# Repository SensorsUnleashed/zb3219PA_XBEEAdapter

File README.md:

# zb3219PA_XBEEAdapter
Adapter for the cheap Aliexpresse zb3219PA module

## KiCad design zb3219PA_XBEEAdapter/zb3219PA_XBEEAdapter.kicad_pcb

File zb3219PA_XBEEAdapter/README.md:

# zb3219PA XBEE Adapter

On chinese sites like aliexpress you can pick up the module zb3219PA, often found by searching for "CC2538 module". This adapterboard will make this cheap board fit boards equiped with the XBEE adapter. This is a cheap way of getting started with the contiki OS.

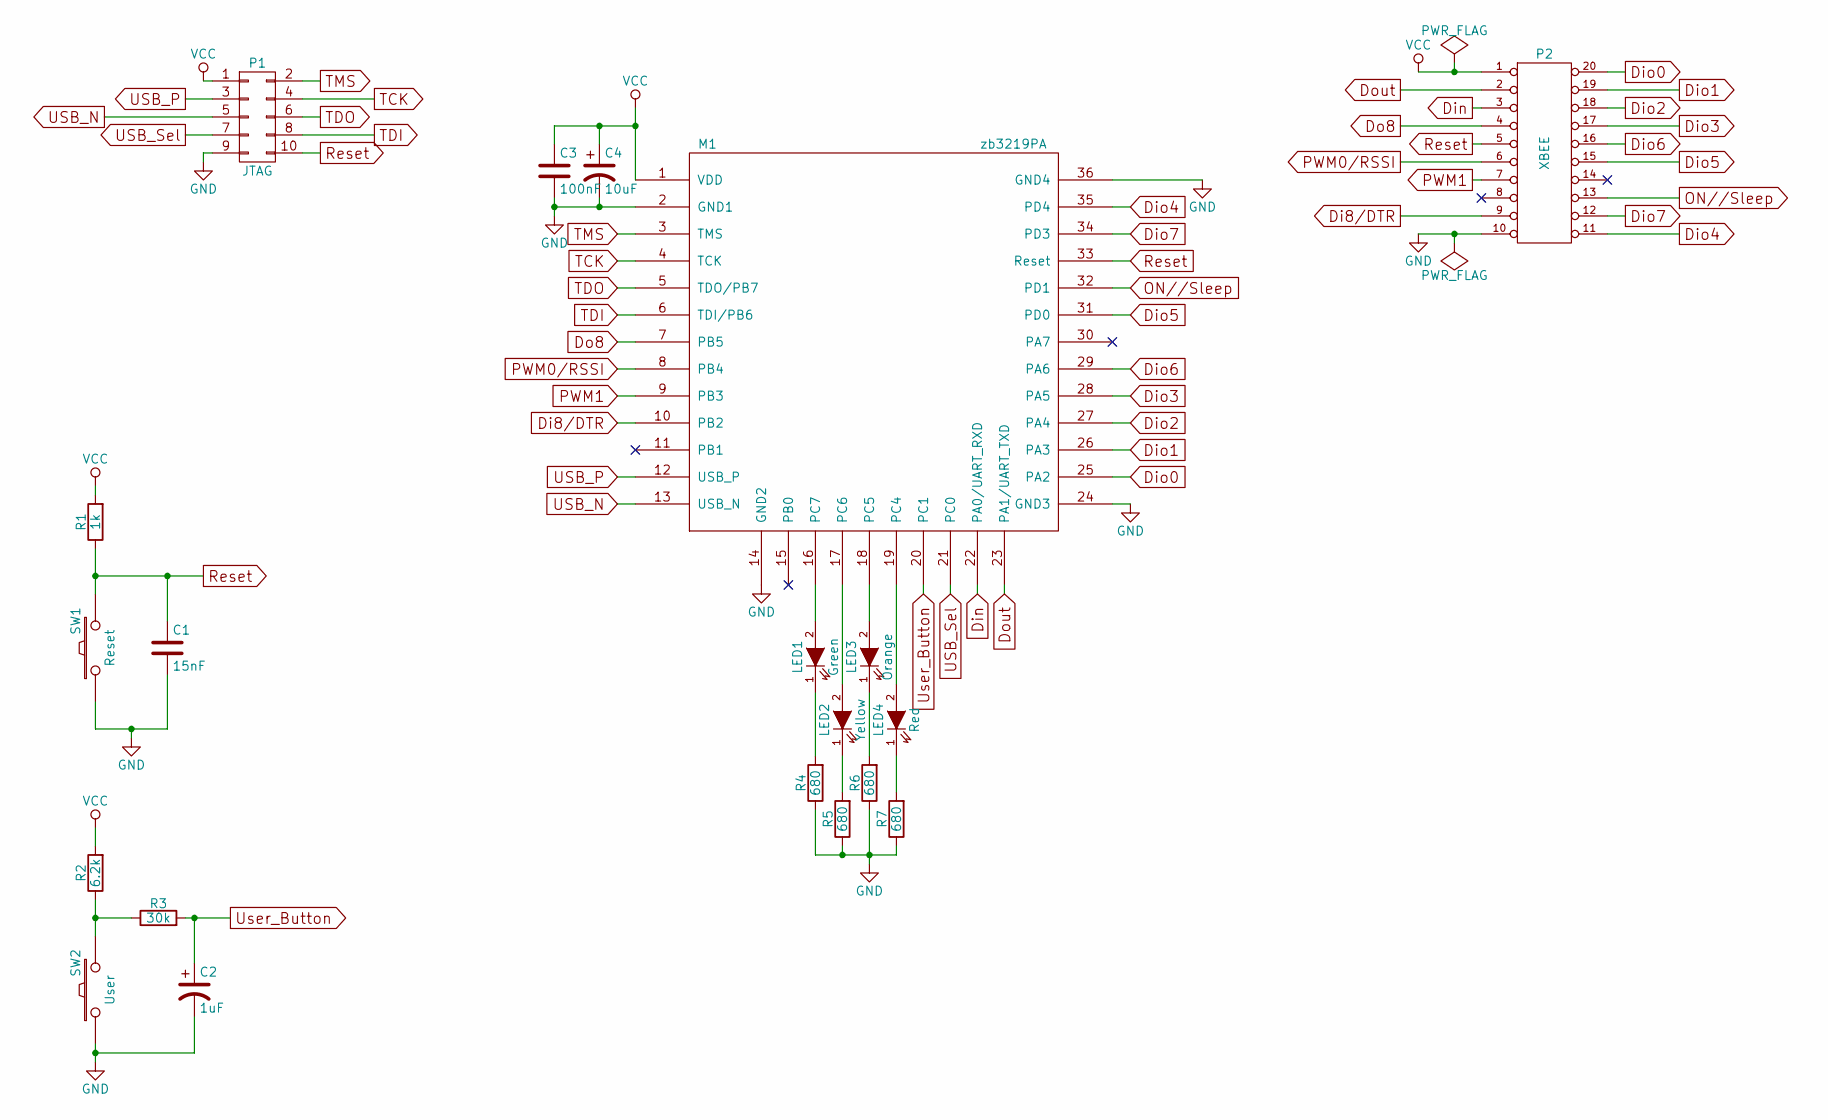
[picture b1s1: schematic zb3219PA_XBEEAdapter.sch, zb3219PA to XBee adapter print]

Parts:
C1: 15nF; C_0805
C2: 1uF; C_0805
C3: 100nF; C_0805
C4: 10uF; C_0805
LED1: Green; LED_0805; Manufacturer Part Number LTST-C171GKT
LED2: Yellow; LED_0805; Manufacturer Part Number LTST-C171KSKT
LED3: Orange; LED_0805; Manufacturer Part Number LTST-C170KFKT
LED4: Red; LED_0805; Manufacturer Part Number LTST-C171KRKT
M1: zb3219PA; zb3219PAmoduleFootprint; Manufacturer Part Number zb3219PA
P1: JTAG; Pin_Header_Straight_2x05_Pitch1.27mm
P2: XBEE; XBEE-HEADER
R1: 1k; R_0805
R2: 6.2k; R_0805
R3: 30k; R_0805
R4, R5, R6, R7: 680; R_0805
SW1: Reset; SW_SPST_B3U-1000P-B; Manufacturer Part Number B3U-1000P-B
SW2: User; SW_SPST_B3U-1000P-B; Manufacturer Part Number B3U-1000P-B

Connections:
Di8/DTR: M1.10 (PB2), P2.9
Din: M1.22 (PA0/UART_RXD), P2.3
Dio0: M1.25 (PA2), P2.20
Dio1: M1.26 (PA3), P2.19
Dio2: M1.27 (PA4), P2.18
Dio3: M1.28 (PA5), P2.17
Dio4: M1.35 (PD4), P2.11
Dio5: M1.31 (PD0), P2.15
Dio6: M1.29 (PA6), P2.16
Dio7: M1.34 (PD3), P2.12
Do8: M1.7 (PB5), P2.4
Dout: M1.23 (PA1/UART_TXD), P2.2
GND: C1.2, C2.2, C3.2, C4.2, M1.2 (GND1), M1.14 (GND2), M1.24 (GND3), M1.36 (GND4), P1.9, P2.10, R4.1, R5.1, R6.1, R7.1, SW1.1, SW2.1
unnamed: LED1.1 (K), R4.2
unnamed: LED1.2 (A), M1.16 (PC7)
unnamed: LED2.1 (K), R5.2
unnamed: LED2.2 (A), M1.17 (PC6)
unnamed: LED3.1 (K), R6.2
unnamed: LED3.2 (A), M1.18 (PC5)
unnamed: LED4.1 (K), R7.2
unnamed: LED4.2 (A), M1.19 (PC4)
unnamed: R2.1, R3.1, SW2.2
ON//Sleep: M1.32 (PD1), P2.13
PWM0/RSSI: M1.8 (PB4), P2.6
PWM1: M1.9 (PB3), P2.7
Reset: C1.1, M1.33 (Reset), P1.10, P2.5, R1.1, SW1.2
TCK: M1.4 (TCK), P1.4
TDI: M1.6 (TDI/PB6), P1.8
TDO: M1.5 (TDO/PB7), P1.6
TMS: M1.3 (TMS), P1.2
USB_N: M1.13 (USB_N), P1.5
USB_P: M1.12 (USB_P), P1.3
USB_Sel: M1.21 (PC0), P1.7
User_Button: C2.1, M1.20 (PC1), R3.2
VCC: C3.1, C4.1, M1.1 (VDD), P1.1, P2.1, R1.2, R2.2

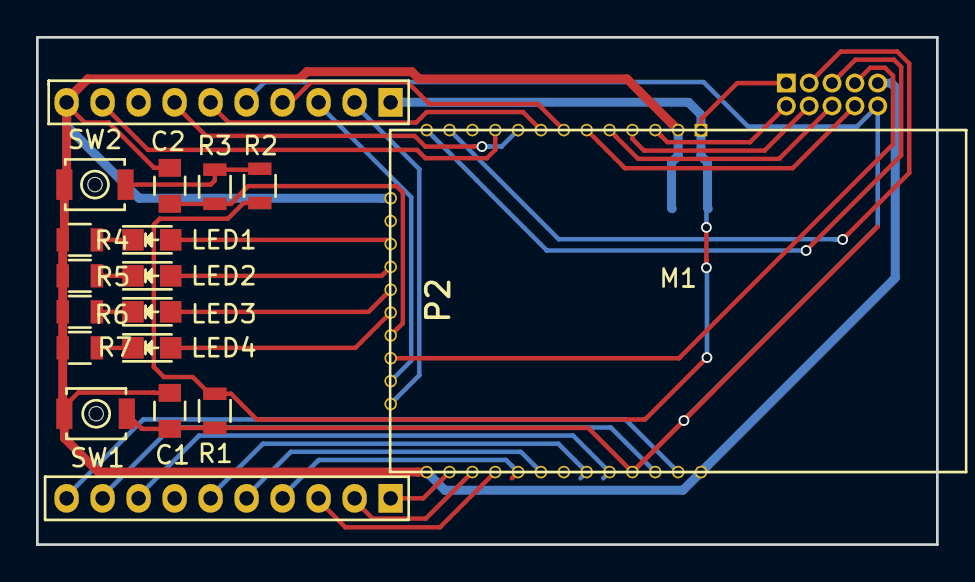
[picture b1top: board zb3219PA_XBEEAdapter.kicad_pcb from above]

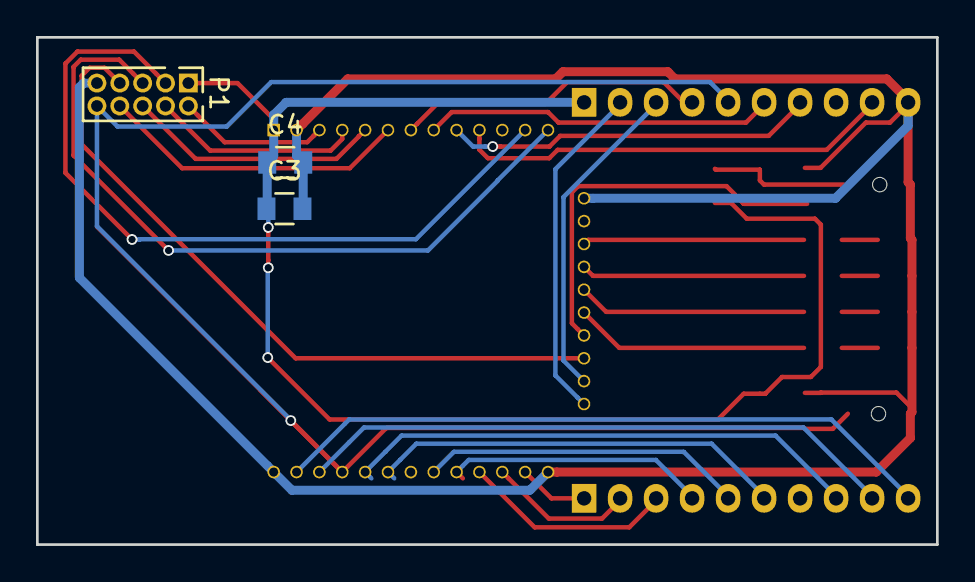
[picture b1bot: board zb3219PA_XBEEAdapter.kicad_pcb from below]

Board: 2 copper layers, 50.0 x 28.2 mm, 20 parts (3 on the bottom side), 35 nets.

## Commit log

2016-11-25 The board has been tested and works.
2017-03-14 Added images
